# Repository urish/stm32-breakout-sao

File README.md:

# STM32 Breakout ShittyAddon

## PCB Renderings

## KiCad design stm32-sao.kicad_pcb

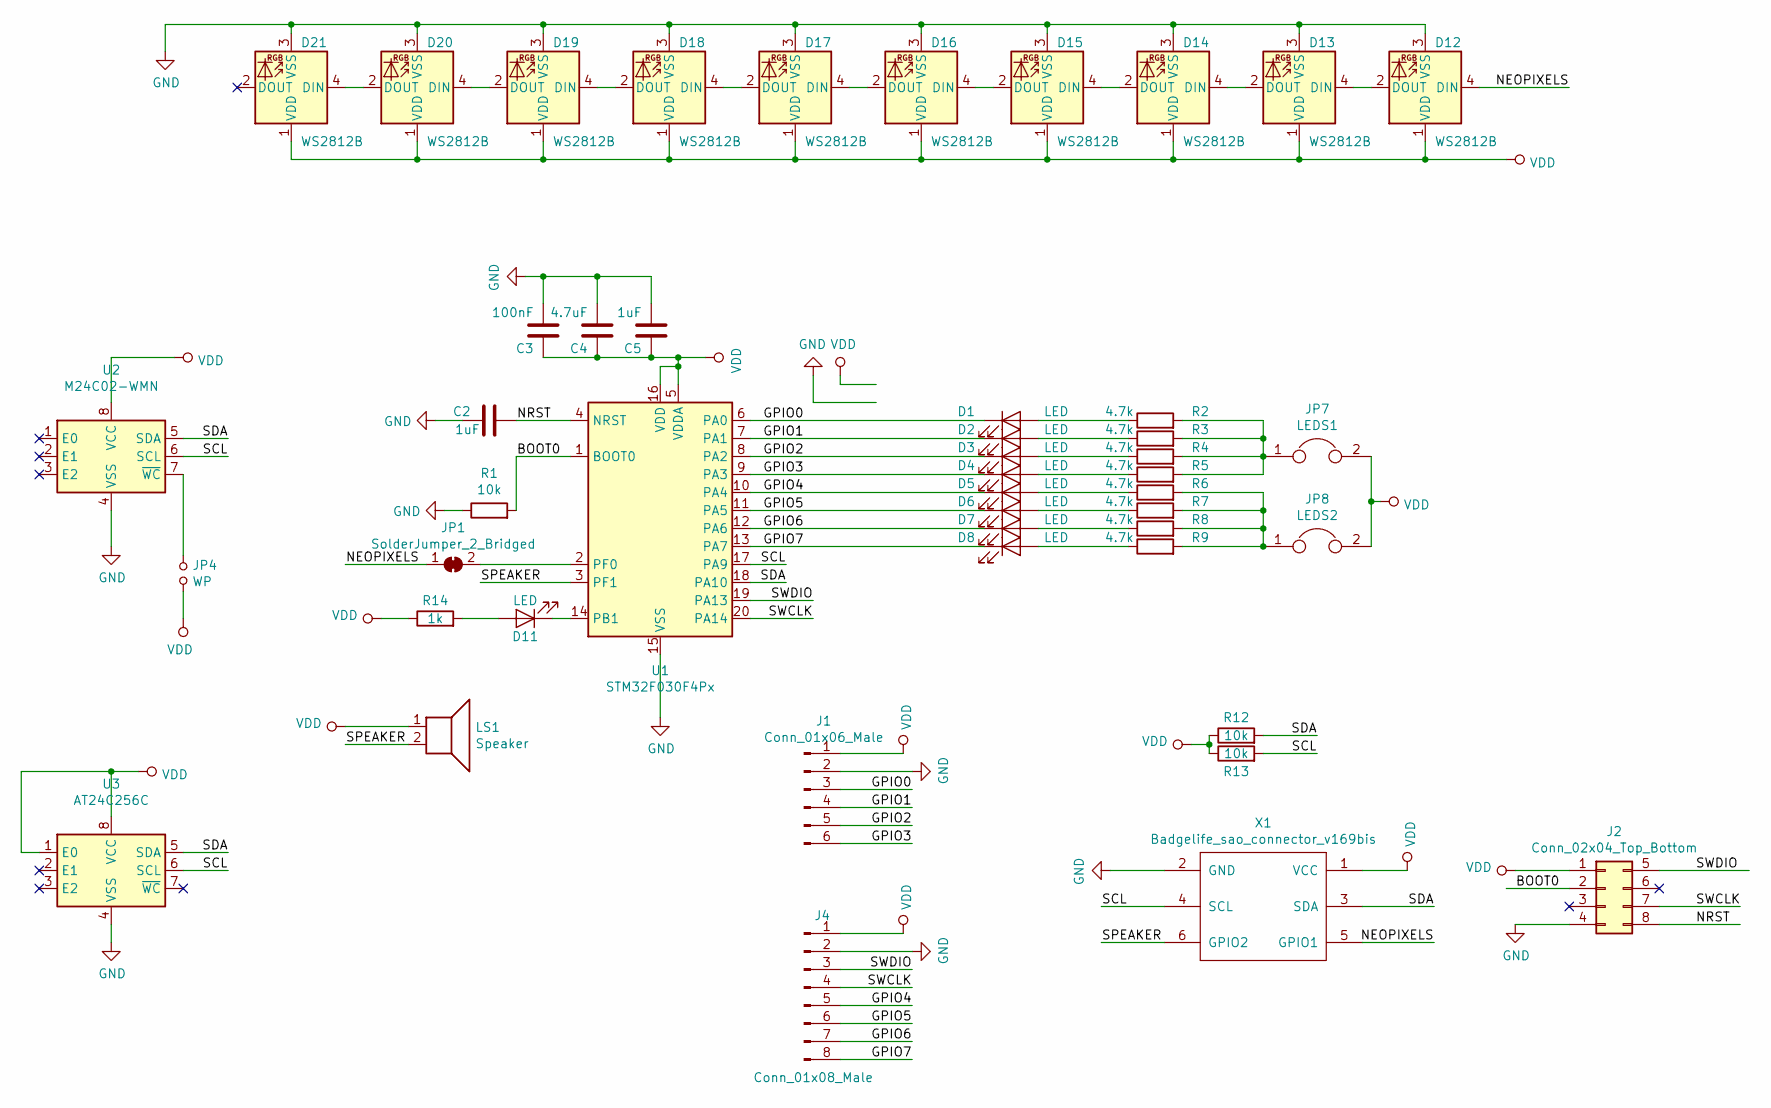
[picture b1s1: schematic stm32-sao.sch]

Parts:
C2, C5: 1uF; C_0402_1005Metric; LCSC Part C52923
C3: 100nF; C_0402_1005Metric; LCSC Part C1525
C4: 4.7uF; C_0402_1005Metric; LCSC Part C23733
D1: LED; LED_0603_1608Metric; LCSC Part C2286
D2, D3, D4, D5, D6, D7, D8: LED; LED_0603_1608Metric
D11: LED; LED_0603_1608Metric; LCSC Part C72041
D12: WS2812B; LED-SMD_4P-L3.5-W3.5-TL_WS2812B; LCSC Part C114583
D13, D14, D15, D16, D17, D18, D19, D20, D21: WS2812B; LED-SMD_4P-L3.5-W3.5-TL_WS2812B
J1: Conn_01x06_Male; PinHeader_1x06_P2.54mm_Vertical
J2: Conn_02x04_Top_Bottom; SOIC_clipProgSmall; JLCPCB BOM 0
J4: Conn_01x08_Male; PinHeader_1x08_P2.54mm_Vertical
JP1: SolderJumper_2_Bridged; SolderJumper-2_P1.3mm_Bridged_Pad1.0x1.5mm
JP4: WP; SolderJumper-2_P1.3mm_Open_RoundedPad1.0x1.5mm; JLCPCB BOM 0
JP7: LEDS1; SolderJumper-2_P1.3mm_Bridged_Pad1.0x1.5mm; JLCPCB BOM 0
JP8: LEDS2; SolderJumper-2_P1.3mm_Bridged_Pad1.0x1.5mm; JLCPCB BOM 0
LS1: Speaker; BUZZER-R14-2P-7.6PITCH
R1: 10k; R_0402_1005Metric; LCSC Part C25744
R2: 4.7k; R_0402_1005Metric; LCSC Part C25900
R3, R4, R5, R6, R7, R8, R9: 4.7k; R_0402_1005Metric
R12, R13: 10k; R_0402_1005Metric
R14: 1k; R_0402_1005Metric; LCSC Part C11702
U1: STM32F030F4Px; TSSOP-20_4.4x6.5mm_P0.65mm; LCSC Part C89040
U2: M24C02-WMN; SOIC-8_3.9x4.9mm_P1.27mm; LCSC Part C7562
U3: AT24C256C; SOIC-8_3.9x4.9mm_P1.27mm; LCSC Part C6482
X1: Badgelife_sao_connector_v169bis; Badgelife-SAOv169-SAO-2x3

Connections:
/BOOT0: J2.2, R1.2, U1.1 (BOOT0)
/GPIO0: D1.1 (K), J1.3, U1.6 (PA0)
/GPIO1: D2.1 (K), J1.4, U1.7 (PA1)
/GPIO2: D3.1 (K), J1.5, U1.8 (PA2)
/GPIO3: D4.1 (K), J1.6, U1.9 (PA3)
/GPIO4: D5.1 (K), J4.5, U1.10 (PA4)
/GPIO5: D6.1 (K), J4.6, U1.11 (PA5)
/GPIO6: D7.1 (K), J4.7, U1.12 (PA6)
/GPIO7: D8.1 (K), J4.8, U1.13 (PA7)
/NEOPIXELS: D12.4 (DIN), JP1.1 (A), X1.5 (GPIO1)
/NRST: C2.2, J2.8, U1.4 (NRST)
/SCL: R13.2, U1.17 (PA9), U2.6 (SCL), U3.6 (SCL), X1.4 (SCL)
/SDA: R12.2, U1.18 (PA10), U2.5 (SDA), U3.5 (SDA), X1.3 (SDA)
/SPEAKER: LS1.2, U1.3 (PF1), X1.6 (GPIO2)
/SWCLK: J2.7, J4.4, U1.20 (PA14)
/SWDIO: J2.5, J4.3, U1.19 (PA13)
GND: C2.1, C3.2, C4.2, C5.2, D12.3 (VSS), D13.3 (VSS), D14.3 (VSS), D15.3 (VSS), D16.3 (VSS), D17.3 (VSS), D18.3 (VSS), D19.3 (VSS), D20.3 (VSS), D21.3 (VSS), J1.2, J2.4, J4.2, R1.1, U1.15 (VSS), U2.4 (VSS), U3.4 (VSS), X1.2 (GND)
unnamed: D1.2 (A), R2.1
unnamed: D2.2 (A), R3.1
unnamed: D3.2 (A), R4.1
unnamed: D4.2 (A), R5.1
unnamed: D5.2 (A), R6.1
unnamed: D6.2 (A), R7.1
unnamed: D7.2 (A), R8.1
unnamed: D8.2 (A), R9.1
unnamed: D11.1 (K), U1.14 (PB1)
unnamed: D11.2 (A), R14.2
unnamed: D12.2 (DOUT), D13.4 (DIN)
unnamed: D13.2 (DOUT), D14.4 (DIN)
unnamed: D14.2 (DOUT), D15.4 (DIN)
unnamed: D15.2 (DOUT), D16.4 (DIN)
unnamed: D16.2 (DOUT), D17.4 (DIN)
unnamed: D17.2 (DOUT), D18.4 (DIN)
unnamed: D18.2 (DOUT), D19.4 (DIN)
unnamed: D19.2 (DOUT), D20.4 (DIN)
unnamed: D20.2 (DOUT), D21.4 (DIN)
unnamed: JP1.2 (B), U1.2 (PF0)
unnamed: JP4.1, U2.7 (~WC)
unnamed: JP7.1, R2.2, R3.2, R4.2, R5.2
unnamed: JP8.1, R6.2, R7.2, R8.2, R9.2
VDD: C3.1, C4.1, C5.1, D12.1 (VDD), D13.1 (VDD), D14.1 (VDD), D15.1 (VDD), D16.1 (VDD), D17.1 (VDD), D18.1 (VDD), D19.1 (VDD), D20.1 (VDD), D21.1 (VDD), J1.1, J2.1, J4.1, JP4.2, JP7.2, JP8.2, LS1.1, R12.1, R13.1, R14.1, U1.5 (VDDA), U1.16 (VDD), U2.8 (VCC), U3.1 (E0), U3.8 (VCC), X1.1 (VCC)

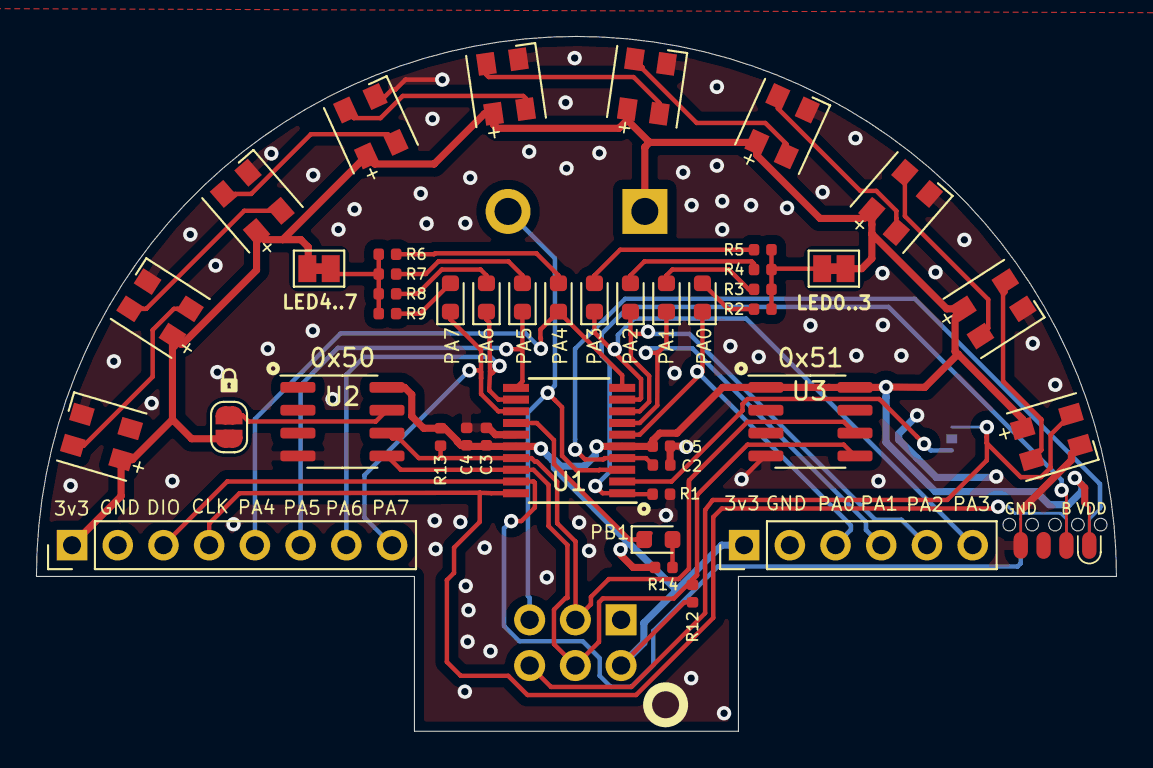
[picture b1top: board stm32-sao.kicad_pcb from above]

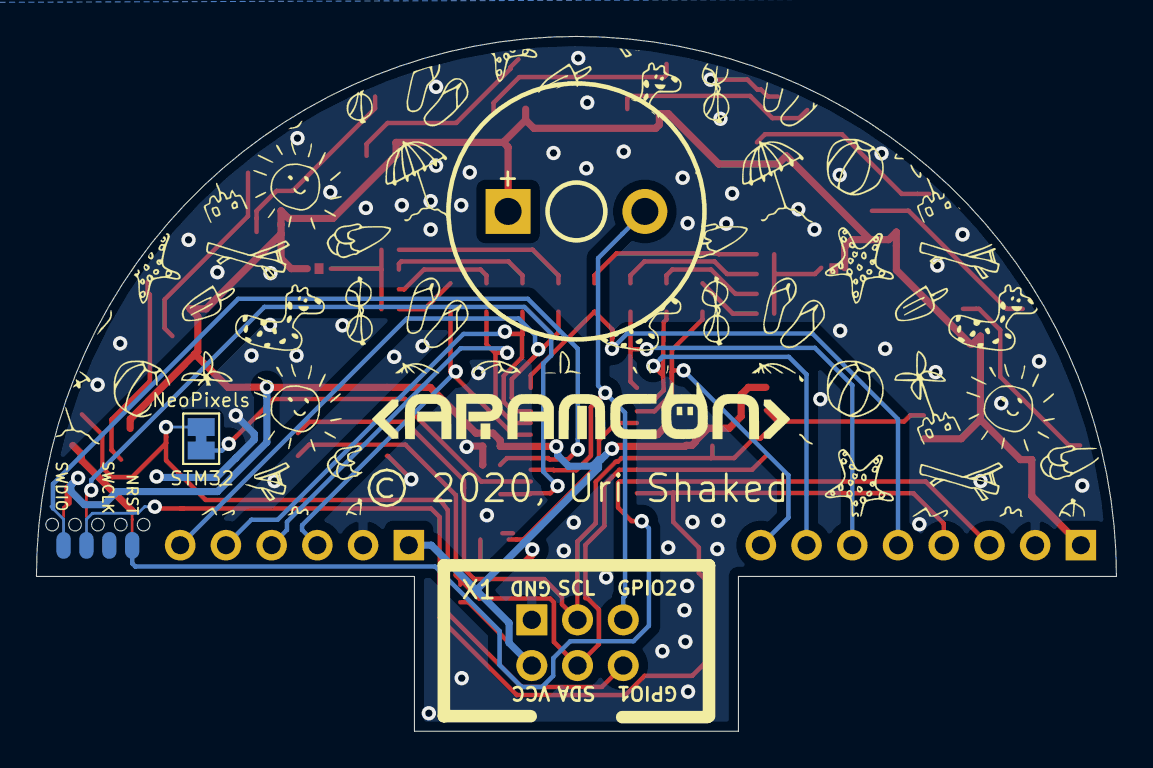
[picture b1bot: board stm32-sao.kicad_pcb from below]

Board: 2 copper layers, 60.0 x 38.6 mm, 50 parts (4 on the bottom side), 41 nets.

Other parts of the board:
Ref**: Val**; background
svg2mod: G***; aramcon-logo-2
svg2mod#2: G***; lock

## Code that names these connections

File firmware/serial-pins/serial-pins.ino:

/* 
 * Control GPIOs over software serial port 
 * Each packet contains the value of 7 pins, and the MSB determines which pin bank we want to index
 * 
 * Copyright (C) 2019, Uri Shaked
 */

#include <SoftwareSerial.h>

#define PIN_RX PF0
#define BAUD_RATE 9600

uint8_t pins[] = { PA0, PA1, PA2, PA3, PA4, PA5, PA6, PA7, PA9, PA10 };
#define NUM_PINS (sizeof(pins) / sizeof(pins[0]))

SoftwareSerial mySerial(PIN_RX, PA0); // RX, TX

void setup() {
  mySerial.begin(BAUD_RATE);
  for (uint8_t pin = 0; pin < NUM_PINS; pin++) {
    pinMode(pins[pin], OUTPUT);
    digitalWrite(pins[pin], HIGH);
  }
}

void loop() { // run over and over
  if (mySerial.available()) {
    uint8_t val = mySerial.read();
    uint8_t pin = val & 0x80 ? 7 : 0;
    for (uint8_t i = 0; i < 7 && pin + i < NUM_PINS; i++) {
      digitalWrite(pins[pin + i], (~val >> i) & 0x1);      
    }
  }
}

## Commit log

2019-09-27 fix: use male connector for SAO
2019-09-27 doc: add borad renderings
2019-09-27 fix: optimize tracks + silk screen for pin 1
    reduce track width, remove unused tracks,
    mark UC pin 1 with a circle on silk screen
2019-10-13 fix: LEDs connected wrong
    they should be connected to VCC, not GND!
2019-10-15 fix: wrong I2C pins
    PA9/PA10 should be connected to the I2C bus instead of PF0/PF1
2019-10-19 fix: silk screen
2019-10-19 feat: sample firmware, control LEDs over UART
2019-10-26 feat: control LEDs in circle CircuitPython demo
2020-01-15 feat: second version of the PCB
    1. Upgrade #badgelife Shitty Add-On connector to V1.69bis
    2. Add 10 NeoPixels (WS2812B-Mini)
    3. Add a small 7mm speaker
    4. Redesign the board
    5. Add a second I2C EEPROM
    6. Add AramCon conference logo
2020-01-15 feat: add background pattern to back side

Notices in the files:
stm32-sao.kicad_pcb:
© 2020, Uri Shaked
